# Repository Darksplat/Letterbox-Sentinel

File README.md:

# Letterbox Sentinel

Letterbox Sentinel is a battery-powered ESP8266/Wemos D1 Mini mail detector for Home Assistant using MQTT Discovery.

Current firmware: **v3.1.0**

## What it does

- Detects each separate delivery through the mail slot using an IR break-beam sensor.
- Supports multiple deliveries per day, even while `Mail Waiting` is already ON.
- Keeps a persistent `Mail Waiting` state until the mailbox is emptied.
- Keeps a persistent lifetime delivery counter.
- Records the most recent mail detection time.
- Supports NFC-driven collection through Home Assistant, including the collector name.
- Publishes BME280 temperature, humidity and sea-level-corrected pressure.
- Monitors a 2S 18650 battery pack through A0.
- Publishes Wi-Fi, network and device diagnostics to Home Assistant.
- Supports Arduino OTA updates.
- Uses timed deep sleep outside delivery hours to extend battery life.
- Uses DHCP by default so it can work on different home-network address ranges.

## Daily operating schedule

### Monday-Saturday

- **07:30**: IR mail monitoring begins.
- **17:00**: IR monitoring ends and scheduled deep-sleep operation begins.
- Every genuine delivery:
  - sets `Mail Waiting` to ON;
  - increments the persistent delivery counter;
  - updates `Last Mail Detected`;
  - publishes a mail event to MQTT;
  - turns the IR emitter off for 30 seconds;
  - automatically rearms the IR detector after the lockout.

The detector continues to accept later deliveries during the same day. Mail does not need to be collected before another delivery can be detected.

### Sunday

The IR system remains disabled and the ESP8266 uses scheduled deep sleep.

Deep sleep is performed in chunks of up to 60 minutes. The final sleep before 07:30 is shortened so the device wakes close to the monitoring start time.

## Mail Waiting and delivery counting

`Mail Waiting` and the delivery detector are deliberately independent:

- `Mail Waiting` answers: **Is there uncollected mail in the box?**
- The delivery counter answers: **How many separate deliveries have been detected?**

Example:

```text
10:00 Australia Post delivery
Mail Waiting: ON
Letter Counter: 1

14:00 Courier delivery
Mail Waiting: still ON
Letter Counter: 2

16:00 NFC collection
Mail Waiting: OFF
Letter Counter: still 2
```

Clearing `Mail Waiting` does not reset the lifetime counter.

## Hardware

- Wemos/LOLIN D1 Mini (ESP8266)
- BME280 environmental sensor
- IR break-beam receiver
- IR emitter
- BC547 transistor for IR emitter switching
- 2S 18650 battery pack
- TRACO Power TSR 1-2433 3.3 V switching regulator
- 330 kΩ / 100 kΩ battery voltage divider
- Optional 100 nF capacitor on A0
- D0/GPIO16 to RST connection for timed deep-sleep wake

### Custom PCB

A custom 2-layer KiCad carrier PCB has been developed for Letterbox Sentinel. The hardware design is documented under [`hardware/`](hardware/README.md).

Key PCB features:

- Approximately **64 mm × 50 mm**.
- Socketed Wemos D1 Mini for serviceability.
- Socketed **TRACO TSR 1-2433** 3.3 V regulator.
- Choice of **5.5 × 2.1 mm centre-positive barrel jack** or **AMASS XT60PW-F female** battery input.
- Raw 2S battery monitoring before regulation using the 330 kΩ / 100 kΩ divider.
- 1000 µF / 25 V reservoir capacitor on the 3.3 V rail.
- BC547-switched IR transmitter output.
- Female sockets for IR TX, IR RX and BME280.
- Bottom-layer GND copper plane.
- Through-hole construction for practical hand assembly and repair.

The routed board passed KiCad DRC with **0 errors and 0 unconnected pads** during the manufacturing review.

## Pinout

| Function | D1 Mini pin |
|---|---|
| BME280 SCL | D1 |
| BME280 SDA | D2 |
| IR receiver signal | D5 |
| IR emitter transistor control | D6 |
| Battery voltage | A0 |
| Deep-sleep wake | D0/GPIO16 → RST |

## IR emitter switching

D6 is a control signal only. Do not power the IR emitter directly from D6.

```text
D6 ---- 4.7k ---- BC547 base
BC547 emitter ---- GND
BC547 collector -- IR emitter negative
IR emitter positive -- 3.3 V rail
```

The IR receiver remains connected to D5.

## Battery monitoring

Current external divider:

```text
Battery + ---- 330k ----+---- A0
                        |
                      100k
                        |
Battery - ------------- GND
```

The current firmware uses:

```cpp
const float ADC_FULL_SCALE_V = 3.20F;
const float BATTERY_DIVIDER_RATIO = 5.35F;
const float BATTERY_CALIBRATION = 0.975F;
```

These values were calibrated against a multimeter on the installed Wemos D1 Mini and divider network. Other boards may require recalibration.

## BME280 pressure

Pressure is corrected to sea level using the configured site altitude:

```cpp
const float SITE_ALTITUDE_METERS = 230.0F;
```

The default is approximately 230 m above sea level for Maiden Gully, Victoria. Change this value for another installation location.

## Network configuration

Firmware v3.1.0 uses **DHCP by default**:

```cpp
const bool USE_STATIC_IP = false;
```

This means the device can join networks using address ranges such as:

- `192.168.0.x`
- `192.168.1.x`
- `10.x.x.x`
- `172.16.x.x`

For a stable address, the recommended approach is to leave DHCP enabled and create a DHCP reservation in the router.

Static addressing is optional. The static IP, gateway, subnet and DNS values are ignored unless:

```cpp
const bool USE_STATIC_IP = true;
```

## MQTT broker address

The public firmware defaults to:

```cpp
const char* MQTT_HOST = "homeassistant.local";
```

This may be replaced with:

- the MQTT broker hostname;
- the Home Assistant hostname if the broker runs there; or
- the broker's IP address.

The MQTT broker does not have to run on Home Assistant.

## NFC mail collection

The NFC tag is read by a phone running Home Assistant. It is not read directly by the Wemos.

Home Assistant should publish to:

```text
letterbox_sentinel/command/mail_collected
```

Example payload:

```json
{"collector":"Leigh"}
```

The firmware then:

- clears `Mail Waiting`;
- stores and publishes the collector name;
- stores and publishes the collection time;
- keeps the lifetime delivery counter unchanged.

The manual **Clear Mail Waiting** button performs the same state clear without requiring NFC.

## Home Assistant MQTT Discovery

The firmware automatically creates sensors, binary sensors and buttons in Home Assistant using MQTT Discovery.

### Stable identifier rule

From firmware **v2.2.0 onward**, MQTT Discovery identifiers are treated as a stable API:

- Discovery object IDs remain unchanged across firmware revisions.
- `unique_id` values remain unchanged across firmware revisions.
- Display names, icons, units, calibration and firmware logic may change without changing identifiers.
- If an entity must be removed or replaced, the obsolete retained MQTT Discovery topic must be cleared.

This prevents duplicate and orphaned Home Assistant entities during upgrades.

## Home Assistant controls

Current controls include:

- Clear Mail Waiting
- Reset Letter Counter
- Test Mail Detection
- Restart
- Enter Safe Mode
- Exit Safe Mode

The **Test Mail Detection** button creates a test event but does not start the 30-second physical IR lockout.

## Home Assistant entities

Important entities include:

- Mail Waiting
- Mail Slot Beam
- IR Emitter Active
- Letter Counter
- Last Mail Detected
- Last Collected By
- Last Collection Time
- Battery
- Battery Voltage
- Low Battery
- Temperature
- Humidity
- Sea Level Pressure
- Wi-Fi Signal
- Uptime
- IP Address
- Wi-Fi SSID
- MAC Address
- Gateway
- DNS Server
- Reset Reason
- Firmware
- Safe Mode
- Network Time Valid

## Required Arduino libraries

Install using **Arduino IDE → Library Manager**:

- PubSubClient
- ArduinoJson 7
- Adafruit BME280 Library
- Adafruit Unified Sensor

Also install ESP8266 board support and select the correct Wemos/LOLIN D1 Mini board.

## Firmware setup

Open:

```text
Letterbox_Sentinel_v3_1_0.ino
```

Edit only the clearly marked:

```cpp
// USER CONFIGURATION - EDIT THIS SECTION ONLY
```

At minimum, configure:

- Wi-Fi SSID and password;
- MQTT host, port, username and password;
- OTA password;
- site altitude;
- operating hours if different;
- DHCP or optional static IP settings.

The public repository intentionally contains placeholders instead of private Wi-Fi, MQTT and OTA credentials.

## Security

Never commit real Wi-Fi, MQTT or OTA passwords to a public repository.

Use placeholders such as:

```cpp
const char* WIFI_SSID = "CHANGE_WIFI_SSID";
const char* WIFI_PASSWORD = "CHANGE_WIFI_PASSWORD";
const char* MQTT_PASSWORD = "CHANGE_MQTT_PASSWORD";
const char* OTA_PASSWORD = "CHANGE_OTA_PASSWORD";
```

## Additional setup guide

See:

```text
Letterbox_Sentinel_v3_1_0_SETUP.md
```

for detailed first-time installation, Arduino IDE, DHCP/static IP, MQTT and testing instructions.

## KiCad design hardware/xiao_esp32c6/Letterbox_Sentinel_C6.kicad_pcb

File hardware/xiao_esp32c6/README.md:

# Letterbox Sentinel — XIAO ESP32-C6 carrier revision C6-2

This is a separate hardware revision for the **Seeed Studio XIAO ESP32-C6**, with a vertical **AMASS XT60PB-M** battery connector and **JST-XH** IR connectors, retaining the 64 × 50 mm carrier outline and 2S battery inputs. The original ESP8266 design remains in the parent hardware directory.

## Changes

- Two removable 1×7 sockets, 2.54 mm pitch, **17.78 mm row spacing**. USB faces the bottom edge marked USB THIS EDGE. With USB facing the bottom edge, D0 is the bottom pin of the right-hand physical row and 5V is the bottom pin of the left-hand physical row. Use female sockets tall enough to clear the components underneath the XIAO; verify clearance with the actual board before fabrication.
- Remove BME280 connector and its I2C nets. No temperature, humidity or pressure sensing.
- Remove ESP8266 D0-to-RST wake connection.
- Keep the IR transmitter, receiver, BC547 switching circuit and battery divider.
- Add C2, a 100 nF ceramic capacitor, across the ADC divider's lower resistor.
- Replace the **TSR 1-2433** with **TSR 1-2450 (5 V)**. Its output supplies the XIAO 5V pin. The XIAO 3V3 output supplies the IR circuit and C1. Do not fit the old 3.3 V regulator to this revision.
- Correct D1's physical footprint numbering: **pad 1 = cathode = VIN_PROTECTED; pad 2 = anode = BAT_RAW+**. The diode's band faces the protected regulator supply.
- Correct Q1 to BC547's C-B-E pin order: **pad 1 collector = IR_TX_SW_GND; pad 2 base = Q1_BASE; pad 3 emitter = GND**. Verify the actual transistor manufacturer's pinout when assembling.
- Reroute both copper layers; the original ground pour is replaced by routed ground connections. A provisional clear area is reserved near the module's antenna end. RF clearance and reception must be confirmed with the actual XIAO and letterbox enclosure; this is not a manufacturer-approved RF layout.

## Connector revision C6-2

J2 is **AMASS XT60PB-M**, a male vertical PCB connector (male metal pins). The custom footprint has 7.20 mm pin spacing, 4.50 mm finished plated holes for the manufacturer's 4.25 mm PCB pins, and a conservative 16 × 8.1 mm housing envelope. It has no horizontal mounting tabs. Pad 1 is battery negative/GND on the chamfered end; pad 2 is battery positive/BAT_RAW+. PCB silkscreen marks + and −. Check polarity against the moulded markings on the actual connector before assembling.

J3 and J4 are keyed **JST-XH 2.50 mm** through-hole headers. XH provides friction retention; it is not a release-tab positive latch. The 2-pin and 3-pin housings prevent TX/RX cable interchange.

| Connector | PCB header | Cable housing | Pin 1 | Pin 2 | Pin 3 |
|---|---|---|---|---|---|
| J3, IR transmitter | B2B-XH-A | XHP-2 | Red, +3V3 | Black, transistor-switched return | — |
| J4, IR receiver | B3B-XH-A | XHP-3 | Red, +3V3 | Black, GND | White/yellow, receiver signal |

Cable pin numbers refer to the numbered PCB pads and must be checked from the mating orientation; a cable viewed from the wire-entry end appears mirrored. Existing Dupont terminals do not fit XH housings. Replace them with XH crimp contacts selected for the sensor wire gauge, or splice on matching pre-crimped pigtails with insulated, strain-relieved joints. JST's XH pitch is **2.50 mm**, not generic 2.54 mm.

Primary connector drawings:
- Amass XT60PB-M V1.2: https://www.tme.com/Document/5b672a89892b7155d7a6087589424d5d/XT60PB-M.pdf
- JST XH: https://www.jst-mfg.com/product/pdf/eng/eXH.pdf
- IR sensor wiring: https://learn.adafruit.com/ir-breakbeam-sensors/arduino

## Firmware pin mapping

| Function | XIAO pin | ESP32-C6 GPIO |
|---|---|---|
| Battery ADC | D0 / A0 | GPIO0 |
| IR receiver | D1 | GPIO1 |
| IR emitter control | D2 | GPIO2 |
| Regulated supply input | 5V | — |
| IR supply output | 3V3 | — |
| Ground | GND | — |

The 330 kΩ / 100 kΩ divider ratio is **4.3**. At 8.4 V battery voltage, ADC voltage is approximately **1.953 V**. The old Wemos calibration factor 5.35 does not apply. Use appropriate ESP32-C6 ADC attenuation, calibrated millivolt readings and multimeter calibration. The 100 nF filter helps the high-impedance divider settle.

## Battery and power limitations

The TSR 1-2450 requires **at least 6.5 V at its input**. The protection diode reduces voltage before the regulator, so operation near the bottom of a 2S pack's discharge range is not guaranteed. A **7.0 V raw-pack low-battery threshold is an initial warning target**, not a hardware cutoff or a substitute for a protected/balanced 2S pack. Confirm voltage under load. This choice sacrifices usable capacity compared with the original 3.3 V regulator; a future low-quiescent-current power revision could improve endurance.

Use only one battery input at a time. Disconnect the carrier's battery supply before connecting the XIAO USB port, because its 5V pin shares USB VBUS. Leave XIAO BAT pads unused: they are for a single lithium cell, not this 2S pack. Confirm the IR modules' supply current is within the XIAO 3V3 regulator's capacity.

## Thread and Home Assistant

This hardware supports the ESP32-C6 radio. **The existing ESP8266 Wi-Fi/MQTT firmware has not been ported and cannot run on this board.** A separate ESP32-C6 firmware implementation is needed for Thread/OpenThread or Matter over Thread, including delivery counting, mail state, collection commands and the operating schedule. Thread alone does not provide Matter entities. A Thread border router is required. The ESP8266 deep-sleep behavior must be revisited because a sleeping device cannot remain available for collection commands.

## Opening and review

Open `Letterbox_Sentinel_C6.kicad_pro` in KiCad 10. The schematic, PCB, symbol library, footprint library and both library tables are included. Keep the entire directory together.

The revision has been checked in KiCad CLI 10.0.6. See `validation/` for the actual reports. Electrical DRC and ERC errors: zero. Unconnected PCB pads: zero. Schematic-to-PCB parity issues: zero. The isolated CLI environment still reports local footprint-library availability warnings; rerun full checks after opening the project in desktop KiCad.

This is a **review revision**, not a released manufacturing package: verify module orientation, socket height, USB access, antenna clearance, IR current draw and regulator behavior with the actual components. No Gerbers are supplied, and old manufacturing files are for the ESP8266 revision only.

## Primary references

- https://wiki.seeedstudio.com/xiao_esp32c6_getting_started/
- https://wiki.seeedstudio.com/xiao_pin_multiplexing_esp32c6/
- https://www.tracopower.com/sites/default/files/products/datasheets/tsr1_datasheet.pdf
- https://www.onsemi.com/download/data-sheet/pdf/bc546-d.pdf

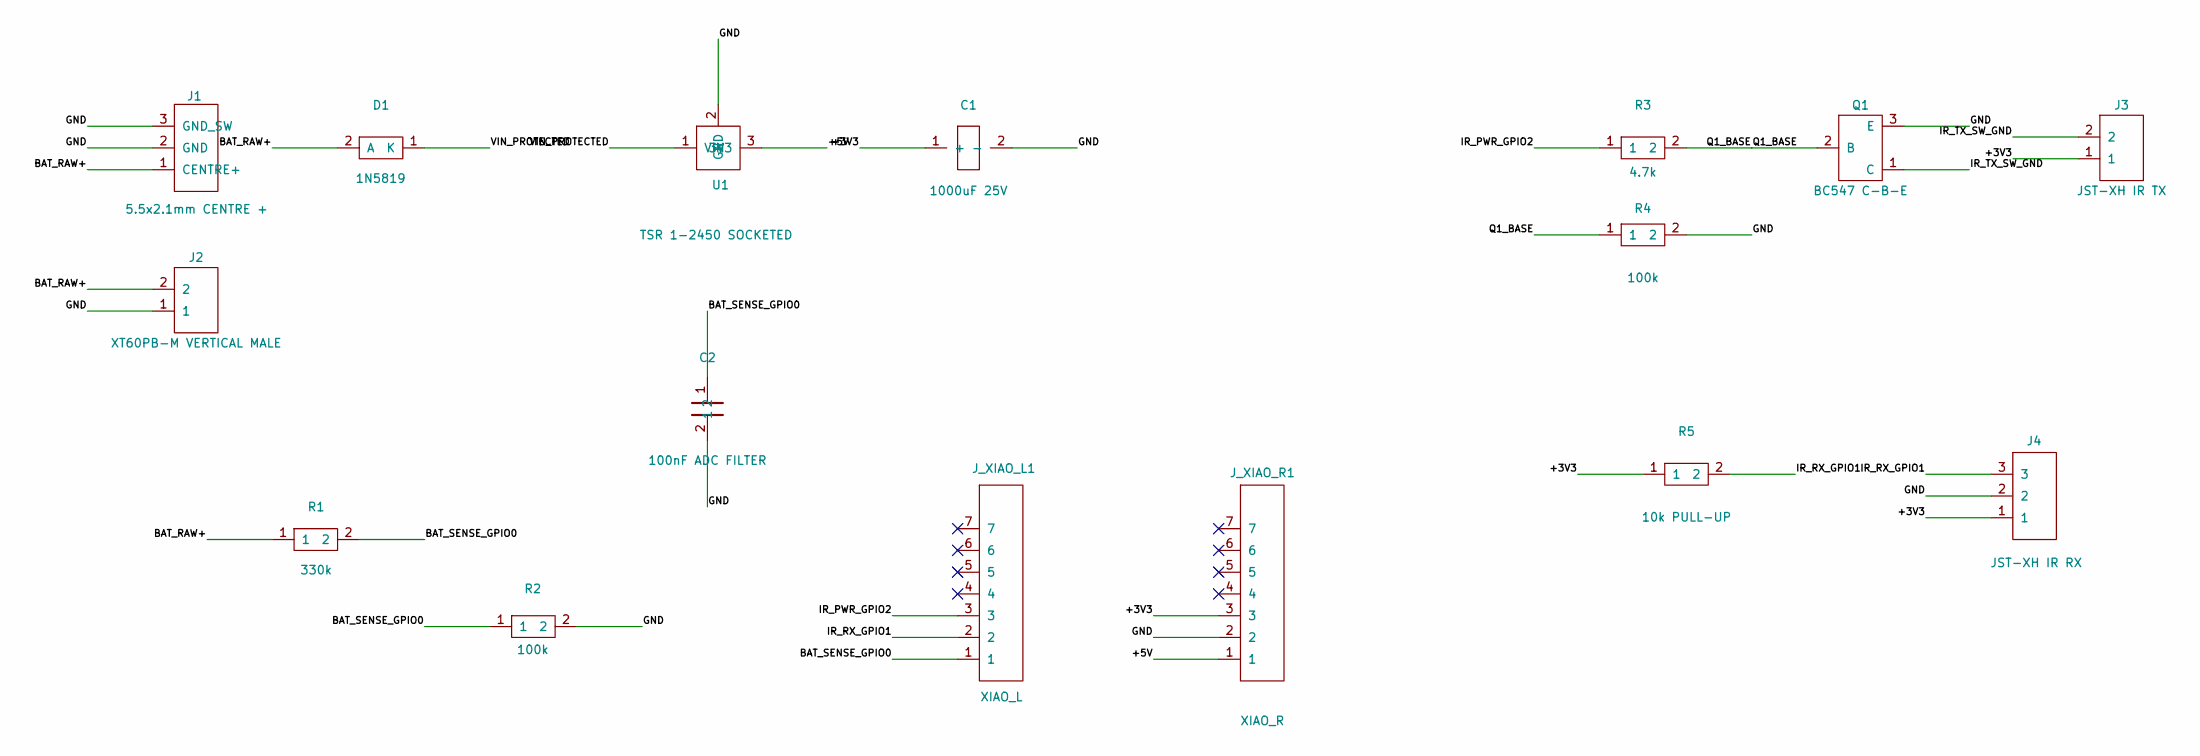
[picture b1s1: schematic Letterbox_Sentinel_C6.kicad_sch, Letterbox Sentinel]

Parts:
C1: 1000uF 25V; CP_Radial_D12.5mm_P5.00mm_C1
C2: 100nF ADC FILTER; C_Disc_D5.0mm_W2.5mm_P5.00mm_C2
D1: 1N5819; D_DO-41_SOD81_P10.16mm_Horizontal_D1
J1: 5.5x2.1mm CENTRE +; BarrelJack_GCT_DCJ200-10-A_Horizontal_J1
J2: XT60PB-M VERTICAL MALE; AMASS_XT60PB-M_1x02_P7.20mm_Vertical_J2
J3: JST-XH IR TX; JST_XH_B2B-XH-A_1x02_P2.50mm_Vertical_J3
J4: JST-XH IR RX; JST_XH_B3B-XH-A_1x03_P2.50mm_Vertical_J4
J_XIAO_L1: XIAO_L; PinSocket_1x07_P2.54mm_Vertical_J_XIAO_L1
J_XIAO_R1: XIAO_R; PinSocket_1x07_P2.54mm_Vertical_J_XIAO_R1
Q1: BC547 C-B-E; TO-92_Inline_Wide_Q1
R1: 330k; R_Axial_DIN0207_L6.3mm_D2.5mm_P10.16mm_Horizontal_R1
R2: 100k; R_Axial_DIN0207_L6.3mm_D2.5mm_P10.16mm_Horizontal_R2
R3: 4.7k; R_Axial_DIN0207_L6.3mm_D2.5mm_P10.16mm_Horizontal_R3
R4: 100k; R_Axial_DIN0207_L6.3mm_D2.5mm_P10.16mm_Horizontal_R4
R5: 10k PULL-UP; R_Axial_DIN0207_L6.3mm_D2.5mm_P10.16mm_Horizontal_R5
U1: TSR 1-2450 SOCKETED; PinSocket_1x03_P2.54mm_Vertical_U1

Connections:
/+3V3: C1.1 (+), J3.1, J4.1, J_XIAO_R1.3, R5.1
/+5V: J_XIAO_R1.1, U1.3 (3V3)
/BAT_RAW+: D1.2 (A), J1.1 (CENTRE+), J2.2, R1.1
/BAT_SENSE_GPIO0: C2.1, J_XIAO_L1.1, R1.2, R2.1
/GND: C1.2 (-), C2.2, J1.2 (GND), J1.3 (GND_SW), J2.1, J4.2, J_XIAO_R1.2, Q1.3 (E), R2.2, R4.2, U1.2 (GND)
/IR_PWR_GPIO2: J_XIAO_L1.3, R3.1
/IR_RX_GPIO1: J4.3, J_XIAO_L1.2, R5.2
/IR_TX_SW_GND: J3.2, Q1.1 (C)
/Q1_BASE: Q1.2 (B), R3.2, R4.1
/VIN_PROTECTED: D1.1 (K), U1.1 (VIN)

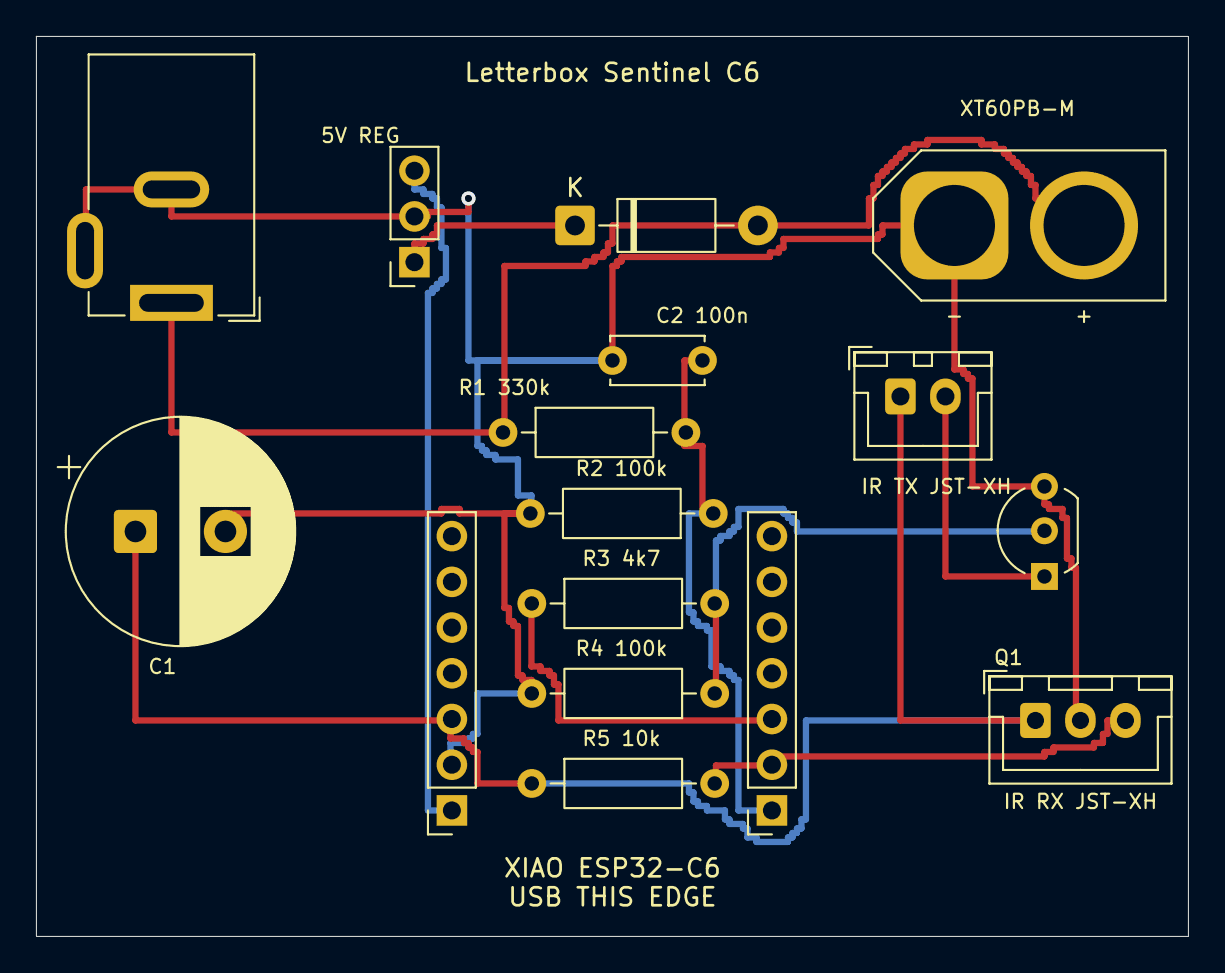
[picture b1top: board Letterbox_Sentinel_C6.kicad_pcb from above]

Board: 2 copper layers, 64.0 x 50.0 mm, 16 parts (0 on the bottom side), 10 nets.

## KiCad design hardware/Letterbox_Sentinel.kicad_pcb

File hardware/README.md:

# Letterbox Sentinel PCB Hardware

This directory contains the KiCad hardware design for the Letterbox Sentinel carrier PCB.

## Current PCB design

- 2-layer FR-4 PCB
- Approximate board size: 64 mm x 50 mm
- Wemos/LOLIN D1 Mini (ESP8266) on removable female headers
- Socketed TRACO Power TSR 1-2433 3.3 V switching regulator
- Dual 2S battery input options: 5.5 x 2.1 mm centre-positive barrel jack or AMASS XT60PW-F female PCB connector
- 1N5819 input protection
- 1000 uF / 25 V 3.3 V reservoir capacitor
- 330 kOhm / 100 kOhm raw-battery divider to A0
- BC547-switched IR transmitter
- Female sockets for IR TX, IR RX and BME280
- Bottom-layer GND copper plane

## Important power note

Use either the barrel jack or XT60 input. Do not connect two independent power sources at the same time.

The battery-voltage divider senses the raw 2S input before regulation.

## KiCad files

The authoritative current schematic and routed PCB are in `kicad/`.

The PCB has been manually routed and checked in KiCad with no DRC errors and no unconnected pads at the final review stage. Any future schematic-to-PCB update should be reviewed carefully so the established component placement and routing are not unintentionally disturbed.

## Manufacturing

`manufacturing/` contains available fabrication drill outputs from the current KiCad project. Gerber files should be regenerated from the authoritative PCB immediately before placing a manufacturing order.

Suggested standard PCB specification:

- 2 layers
- FR-4
- 1.6 mm thickness
- 1 oz copper
- Green solder mask
- White silkscreen
- Lead-free HASL

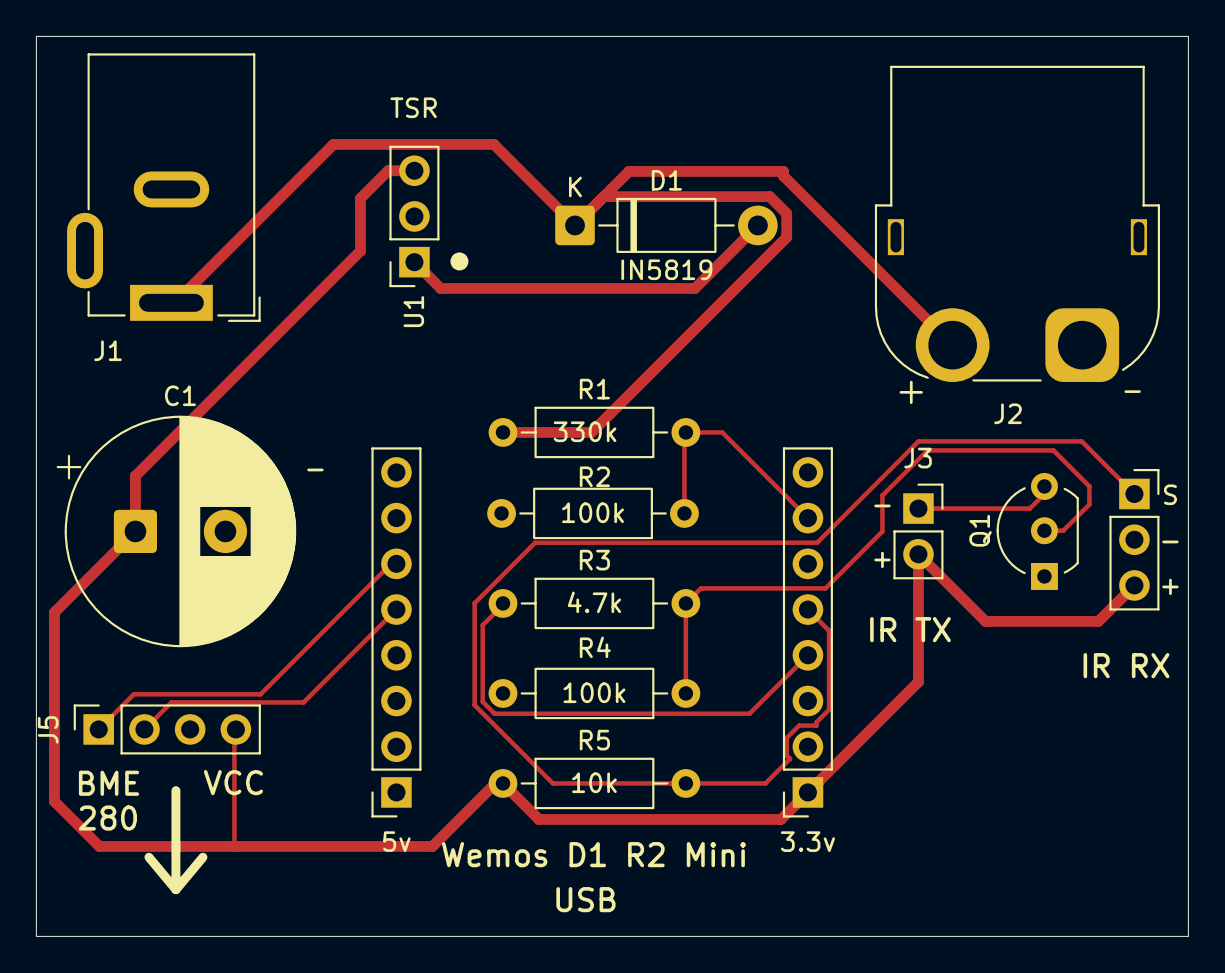
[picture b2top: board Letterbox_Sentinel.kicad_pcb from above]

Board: 2 copper layers, 64.0 x 50.0 mm, 16 parts (0 on the bottom side), 11 nets.

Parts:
3.3v: WEMOS LEFT; PinSocket_1x08_P2.54mm_Vertical
5v: WEMOS RIGHT; PinSocket_1x08_P2.54mm_Vertical
C1: 1000uF 25V; CP_Radial_D12.5mm_P5.00mm
D1: 1N5819; D_DO-41_SOD81_P10.16mm_Horizontal
J1: 5.5x2.1mm CENTRE +; BarrelJack_GCT_DCJ200-10-A_Horizontal
J2: XT60PW-F FEMALE; AMASS_XT60PW-F_1x02_P7.20mm_Horizontal
J3: IR TX FEMALE SOCKET; PinSocket_1x02_P2.54mm_Vertical
J5: BME280 FEMALE SOCKET; PinSocket_1x04_P2.54mm_Vertical
Q1: BC547 C-B-E; TO-92_Inline_Wide
R1: 330k; R_Axial_DIN0207_L6.3mm_D2.5mm_P10.16mm_Horizontal
R2, R4: 100k; R_Axial_DIN0207_L6.3mm_D2.5mm_P10.16mm_Horizontal
R3: 4.7k; R_Axial_DIN0207_L6.3mm_D2.5mm_P10.16mm_Horizontal
R5: 10k PULL-UP; R_Axial_DIN0207_L6.3mm_D2.5mm_P10.16mm_Horizontal
S: IR RX FEMALE SOCKET; PinSocket_1x03_P2.54mm_Vertical
U1: TSR 1-2433 SOCKETED; PinSocket_1x03_P2.54mm_Vertical

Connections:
/+3V3: 3.3v.1, C1.1 (+), J3.2, J5.4, R5.1, S.3, U1.3 (3V3)
/BAT_RAW+: D1.1 (A), J1.1 (CENTRE+), J2.2, R1.1
/BAT_SENSE_A0: 3.3v.7, R1.2, R2.1
/GND: 5v.2, C1.2 (-), J1.2 (GND), J1.3 (GND_SW), J2.1, J5.3, Q1.1 (C), R2.2, R4.2, S.2, U1.2 (GND)
/I2C_SCL_D1: 5v.6, J5.1
/I2C_SDA_D2: 5v.5, J5.2
/IR_PWR_CTL_D6: 3.3v.4, R3.1
/IR_RX_SIG_D5: 3.3v.5, R5.2, S.1
/IR_TX_SW_GND: J3.1, Q1.3 (E)
/Q1_BASE: Q1.2 (B), R3.2, R4.1
/VIN_PROTECTED: D1.2 (K), U1.1 (VIN)

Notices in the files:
hardware/Letterbox_Sentinel.kicad_pcb:
© Jeremy Younger 2026
